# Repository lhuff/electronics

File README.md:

Electronics
===========

Assorted electronics projects and circuits.

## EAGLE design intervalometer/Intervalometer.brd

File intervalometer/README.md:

Intervalometer
===========

Schematic, board file, and 3d printed case (.stl) for an intervalometer designed for use with Canon DSLR cameras (uses 2.5mm remote jack). Has 4 modes (1 second, 1 minute, 30 minutes, and 1 hour) which are displayed on the single seven segment digit.

This project was mostly done to make use of some spare parts and does not include all of the features that a proper intervalometer should have.

Current Version: V1

Other Features to Add:
- Operation with low frequency clock (realtime clock) [Pads for low frequency clock was included, but not wired to XTAL pins]
- Use of RTC module for exact timing [Timing is currently done with the (terrible) internal RC oscillator of the Attiny]
- Regulation of chip power supplies [Vcc is supplied directly from 3.7V LiPo]
- Better display [Either simpler to cut down components or more detailed to provide more info]

This work is licensed under a Creative Commons 
Attribution-NonCommercial-ShareAlike 4.0 International License.

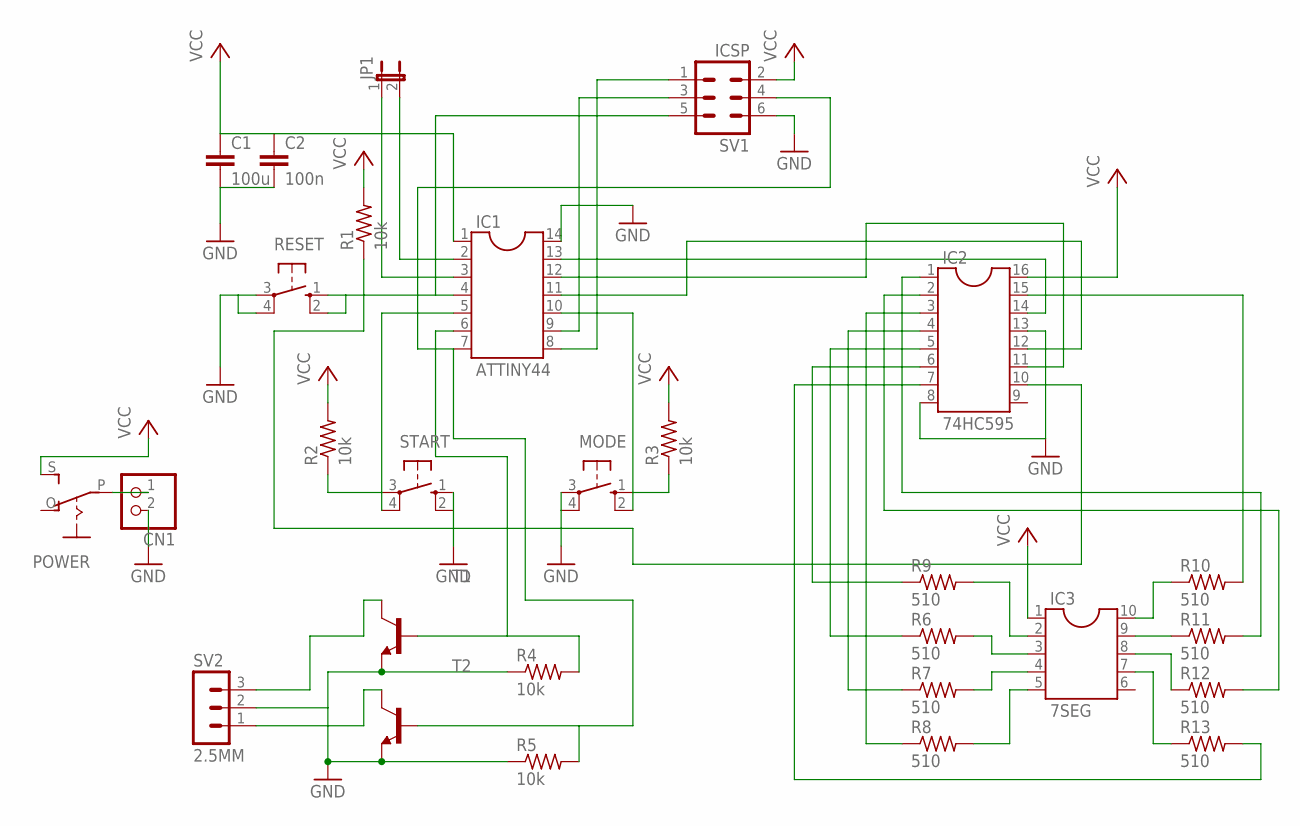
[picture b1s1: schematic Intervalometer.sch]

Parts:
C1: 100u; C2.5-3
C2: 100n; C2.5-3
CN1: JST_2PIN-SMT-RA; JST-PH-2-SMT-RA
IC1: ATTINY44; SOCKET-14
IC2: 74HC595; SOCKET-16
IC3: 7SEG; DIL10
JP1: JP1E; JP1
MODE: 10-XX; B3F-10XX
POWER: EG1218S; EG1218
R1, R2, R3, R4, R5: 10k; 0207/10
R6, R7, R8, R9, R10, R11, R12, R13: 510; 0207/10
RESET: 10-XX; B3F-10XX
START: 10-XX; B3F-10XX
SV1: ICSP; MA03-2
SV2: 2.5MM; MA03-1
T1, T2: -NPN-TO92-EBC; TO92-EBC

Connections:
GND: C1.2, C2.2, CN1.2 (1), IC1.14, IC2.8, IC2.13, MODE.3, MODE.4 (P1), R4.1, R5.1, RESET.3, RESET.4 (P1), START.1 (S), START.2 (S1), SV1.6, SV2.2, T1.E, T2.E
unnamed: IC1.11, IC2.12
unnamed: IC1.4, IC2.10, R1.1, RESET.1 (S), RESET.2 (S1), SV1.5
unnamed: IC1.5, R2.1, START.3, START.4 (P1)
unnamed: IC1.10, MODE.1 (S), MODE.2 (S1), R3.1
unnamed: IC1.13, IC2.14
unnamed: IC1.12, IC2.11
unnamed: IC1.2, JP1.2
unnamed: SV2.1, T2.C
unnamed: SV2.3, T1.C
unnamed: IC1.6, R4.2, T1.B
unnamed: IC1.7, R5.2, SV1.4, T2.B
unnamed: IC3.2, R9.2
unnamed: IC3.3, R6.2
unnamed: IC3.4, R7.2
unnamed: IC3.5, R8.2
unnamed: IC3.10, R10.1
unnamed: IC3.9, R11.1
unnamed: IC3.8, R12.1
unnamed: IC3.7, R13.1
unnamed: IC2.15, R10.2
unnamed: IC2.1, R11.2
unnamed: IC2.2, R12.2
unnamed: IC2.3, R8.1
unnamed: IC2.4, R7.1
unnamed: IC2.5, R6.1
unnamed: IC2.6, R9.1
unnamed: IC2.7, R13.2
unnamed: IC1.9, SV1.3
unnamed: IC1.8, SV1.1
unnamed: IC1.3, JP1.1
unnamed: CN1.1 (2), POWER.P
VCC: C1.1, C2.1, IC1.1, IC2.16, IC3.1, POWER.S, R1.2, R2.2, R3.2, SV1.2

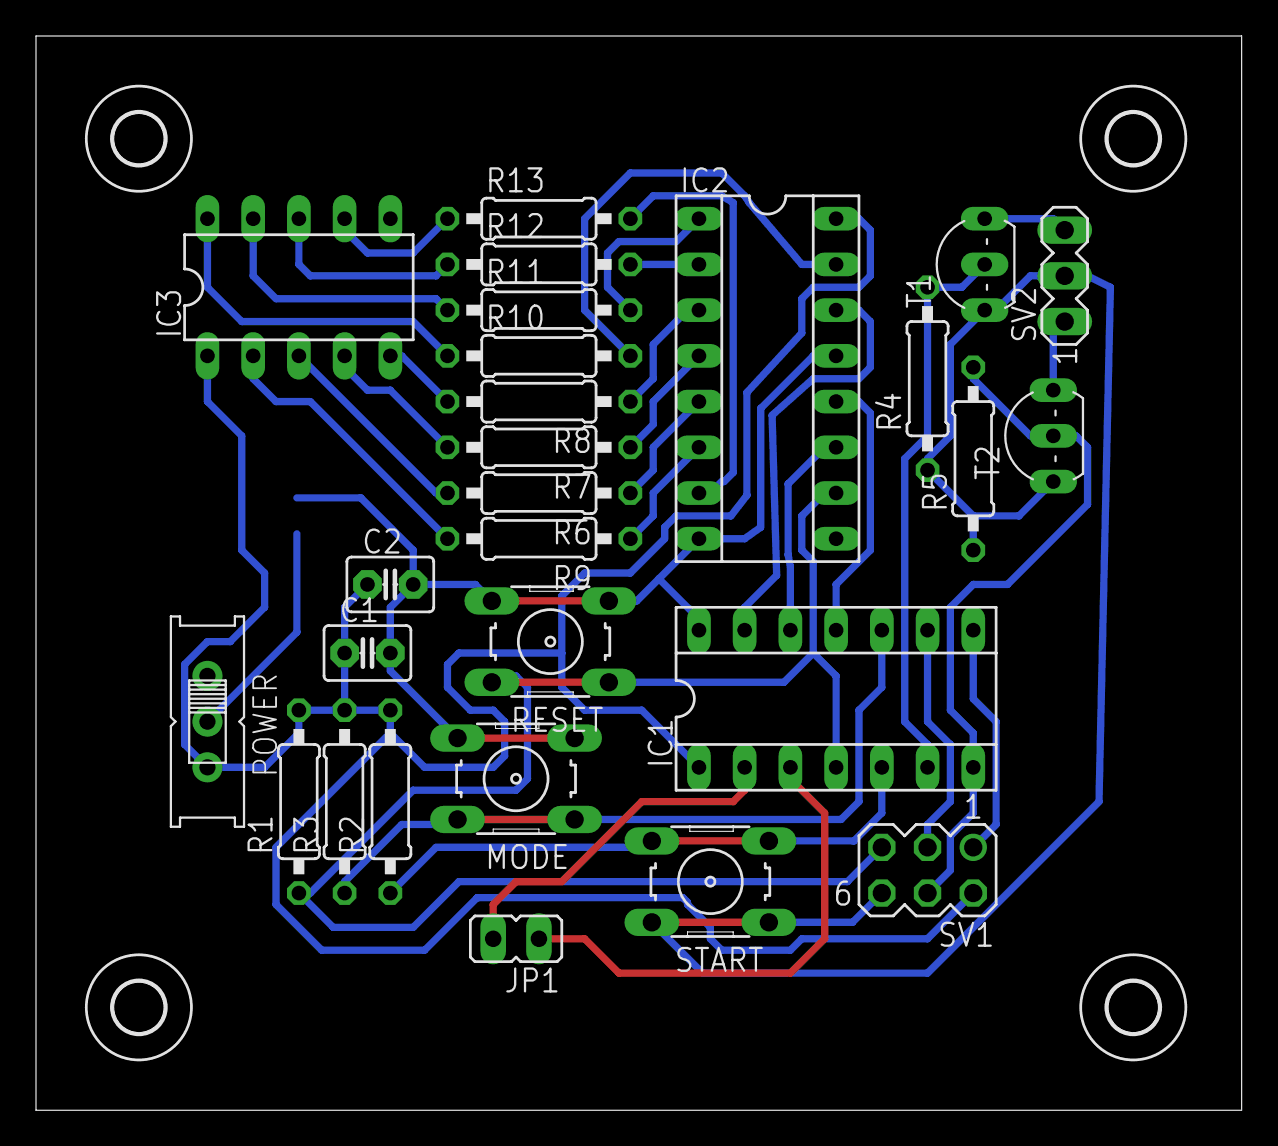
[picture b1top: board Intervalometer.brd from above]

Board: 2 copper layers, 67.0 x 59.7 mm, 32 parts (1 on the bottom side), 33 nets.

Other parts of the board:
U$1, U$2, U$3, U$4: 2,8

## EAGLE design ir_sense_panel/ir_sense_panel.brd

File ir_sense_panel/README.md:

IR Sense Panel
===========

Schematic and board file for a 4x4 infrared distance sensor panel. 

Based off this guide: 
http://www.instructables.com/id/Motion-Sensing-LEDs/?ALLSTEPS

This work is licensed under a Creative Commons 
Attribution-NonCommercial-ShareAlike 4.0 International License.

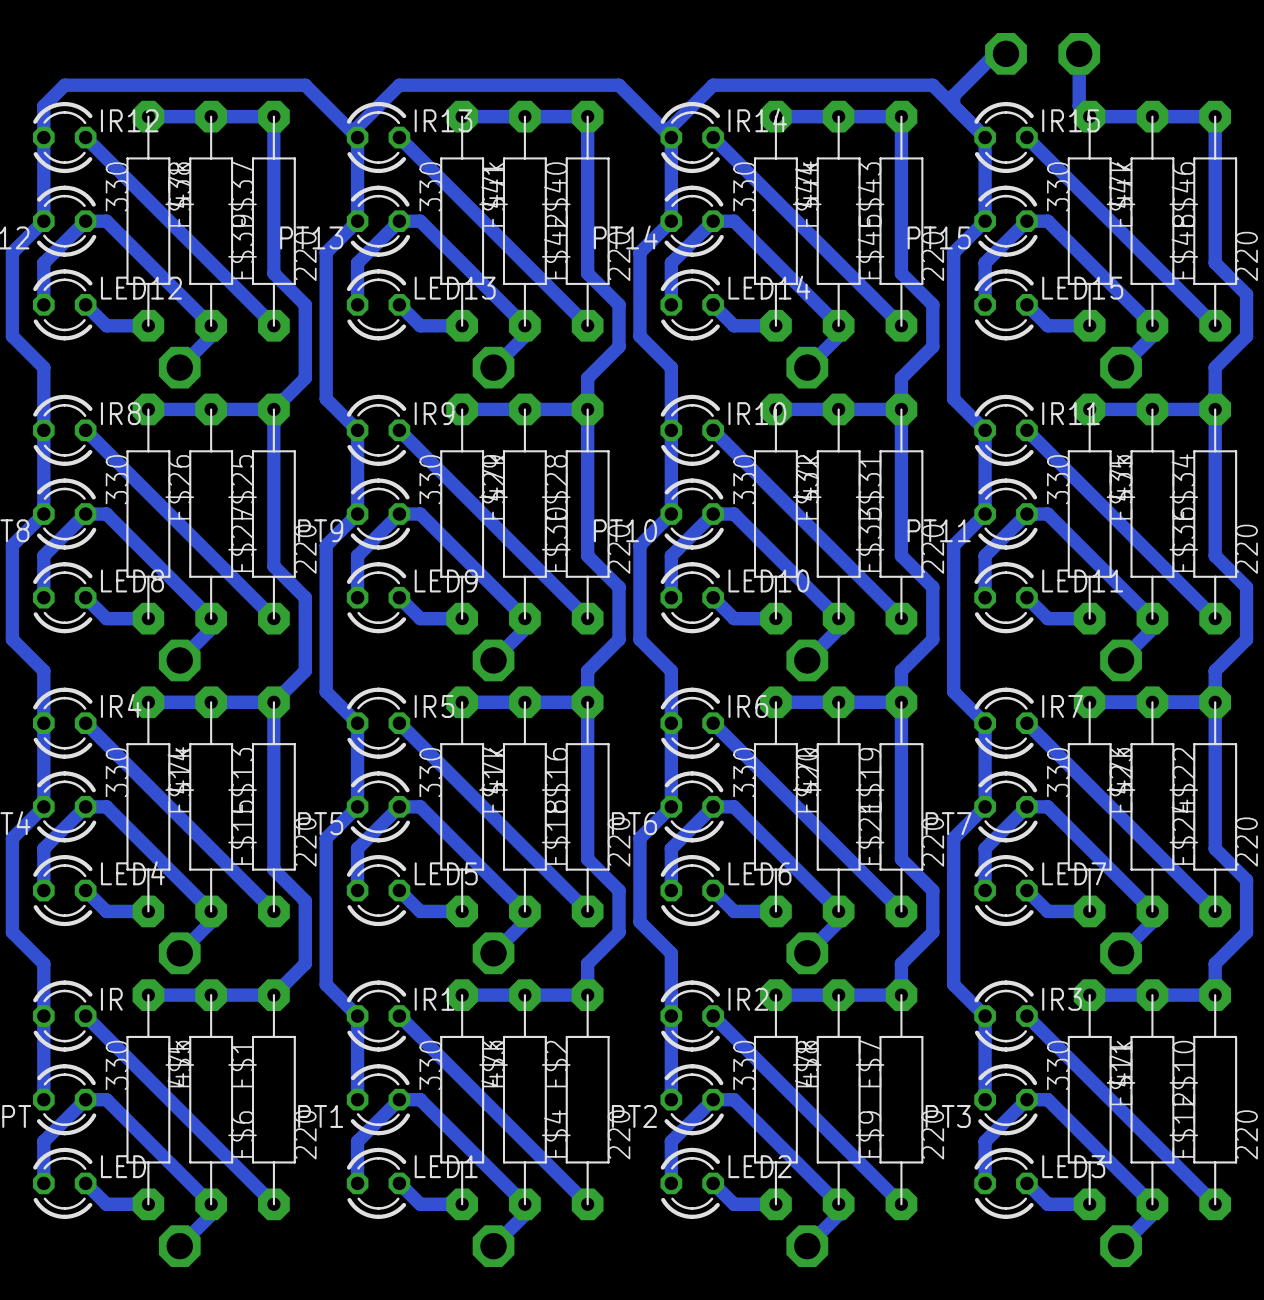
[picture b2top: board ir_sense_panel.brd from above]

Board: 2 copper layers, 114 parts (0 on the bottom side), 50 nets.

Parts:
E$1, E$2, E$7, E$10, E$13, E$16, E$19, E$22, E$28, E$31, E$34, E$37, E$40, E$43, E$46: 47k; RESISTOR_LRG_PAD
E$3, E$5, E$8, E$11, E$14, E$17, E$20, E$23, E$26, E$29, E$32, E$35, E$38, E$41, E$44, E$47: 330; RESISTOR_LRG_PAD
E$4, E$6, E$9, E$12, E$15, E$18, E$21, E$24, E$27, E$30, E$33, E$36, E$39, E$42, E$45, E$48: 220; RESISTOR_LRG_PAD
E$25: RESISTOR_LRG_PAD
E$49, E$50, E$51, E$52, E$53, E$54, E$55, E$56, E$57, E$58, E$59, E$60, E$61, E$62, E$63, E$64: V_PAD_MED
GND: V_PAD_MED
IR, IR1, IR2, IR3, IR4, IR5, IR6, IR7, IR8, IR9, IR10, IR11, IR12, IR13, IR14, IR15: LED3MM
LED, LED1, LED2, LED3, LED4, LED5, LED6, LED7, LED8, LED9, LED10, LED11, LED12, LED13, LED14, LED15: LED3MM
PT, PT1, PT2, PT3, PT4, PT5, PT6, PT7, PT8, PT9, PT10, PT11, PT12, PT13, PT14, PT15: LED3MM
VCC: V_PAD_MED

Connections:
GND: E$1.P$4, E$2.P$4, E$3.P$4, E$4.P$5, E$5.P$4, E$6.P$5, E$7.P$4, E$8.P$4, E$9.P$5, E$10.P$4, E$11.P$4, E$12.P$5, E$13.P$4, E$14.P$4, E$15.P$5, E$16.P$4, E$17.P$4, E$18.P$5, E$19.P$4, E$20.P$4, E$21.P$5, E$22.P$4, E$23.P$4, E$24.P$5, E$25.P$4, E$26.P$4, E$27.P$5, E$28.P$4, E$29.P$4, E$30.P$5, E$31.P$4, E$32.P$4, E$33.P$5, E$34.P$4, E$35.P$4, E$36.P$5, E$37.P$4, E$38.P$4, E$39.P$5, E$40.P$4, E$41.P$4, E$42.P$5, E$43.P$4, E$44.P$4, E$45.P$5, E$46.P$4, E$47.P$4, E$48.P$5, GND.P$1
S$1: E$1.P$5, E$61.P$1, LED.A, PT.A
S$2: E$6.P$4, IR.K
S$3: E$5.P$5, LED.K
S$4: E$2.P$5, E$62.P$1, LED1.A, PT1.A
S$5: E$4.P$4, IR1.K
S$6: E$3.P$5, LED1.K
S$7: E$7.P$5, E$63.P$1, LED2.A, PT2.A
S$8: E$9.P$4, IR2.K
S$9: E$8.P$5, LED2.K
S$10: E$10.P$5, E$64.P$1, LED3.A, PT3.A
S$11: E$12.P$4, IR3.K
S$12: E$11.P$5, LED3.K
S$13: E$13.P$5, E$49.P$1, LED4.A, PT4.A
S$14: E$15.P$4, IR4.K
S$15: E$14.P$5, LED4.K
S$16: E$16.P$5, E$58.P$1, LED5.A, PT5.A
S$17: E$18.P$4, IR5.K
S$18: E$17.P$5, LED5.K
S$19: E$19.P$5, E$59.P$1, LED6.A, PT6.A
S$20: E$21.P$4, IR6.K
S$21: E$20.P$5, LED6.K
S$22: E$22.P$5, E$60.P$1, LED7.A, PT7.A
S$23: E$24.P$4, IR7.K
S$24: E$23.P$5, LED7.K
S$25: E$25.P$5, E$50.P$1, LED8.A, PT8.A
S$26: E$27.P$4, IR8.K
S$27: E$26.P$5, LED8.K
S$28: E$28.P$5, E$57.P$1, LED9.A, PT9.A
S$29: E$30.P$4, IR9.K
S$30: E$29.P$5, LED9.K
S$31: E$31.P$5, E$56.P$1, LED10.A, PT10.A
S$32: E$33.P$4, IR10.K
S$33: E$32.P$5, LED10.K
S$34: E$34.P$5, E$55.P$1, LED11.A, PT11.A
S$35: E$36.P$4, IR11.K
S$36: E$35.P$5, LED11.K
S$37: E$37.P$5, E$51.P$1, LED12.A, PT12.A
S$38: E$39.P$4, IR12.K
S$39: E$38.P$5, LED12.K
S$40: E$40.P$5, E$52.P$1, LED13.A, PT13.A
S$41: E$42.P$4, IR13.K
S$42: E$41.P$5, LED13.K
S$43: E$43.P$5, E$53.P$1, LED14.A, PT14.A
S$44: E$45.P$4, IR14.K
S$45: E$44.P$5, LED14.K
S$46: E$46.P$5, E$54.P$1, LED15.A, PT15.A
S$47: E$48.P$4, IR15.K
S$48: E$47.P$5, LED15.K
VCC: IR.A, IR1.A, IR2.A, IR3.A, IR4.A, IR5.A, IR6.A, IR7.A, IR8.A, IR9.A, IR10.A, IR11.A, IR12.A, IR13.A, IR14.A, IR15.A, PT.K, PT1.K, PT2.K, PT3.K, PT4.K, PT5.K, PT6.K, PT7.K, PT8.K, PT9.K, PT10.K, PT11.K, PT12.K, PT13.K, PT14.K, PT15.K, VCC.P$1

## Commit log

2014-09-02 Added IR Sense Panel
2014-09-02 Fixed IR Panel ReadMe
2014-09-03 Updated README (Minor formatting)
2014-09-03 Further minor formatting
2014-09-03 Minor formatting
2014-11-02 Added board images and readme for intervalometer
2014-11-02 Attempted to fix image issue
2014-11-02 Added second intervalometer board image to readme
2014-11-02 Update readme text
    Added more info in first paragraph
2014-11-02 Added intervalometer board and schematic files
2014-12-19 Added case stl files
    Added STL files for case bottom and lid (version 1)
2014-12-19 Added firmware V1
    Added test firmware, currently only seven segment display and mode
    select is implemented
2014-12-19 Added printout of eagle board layout
